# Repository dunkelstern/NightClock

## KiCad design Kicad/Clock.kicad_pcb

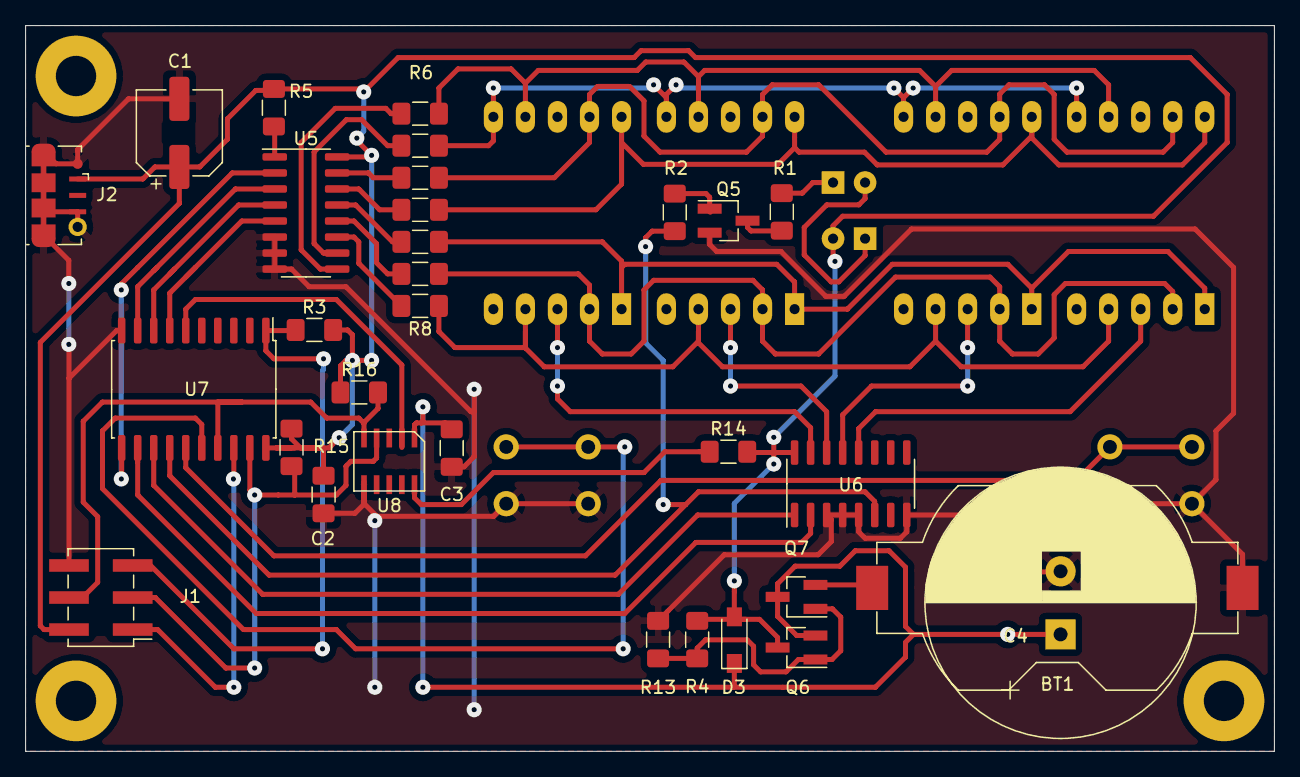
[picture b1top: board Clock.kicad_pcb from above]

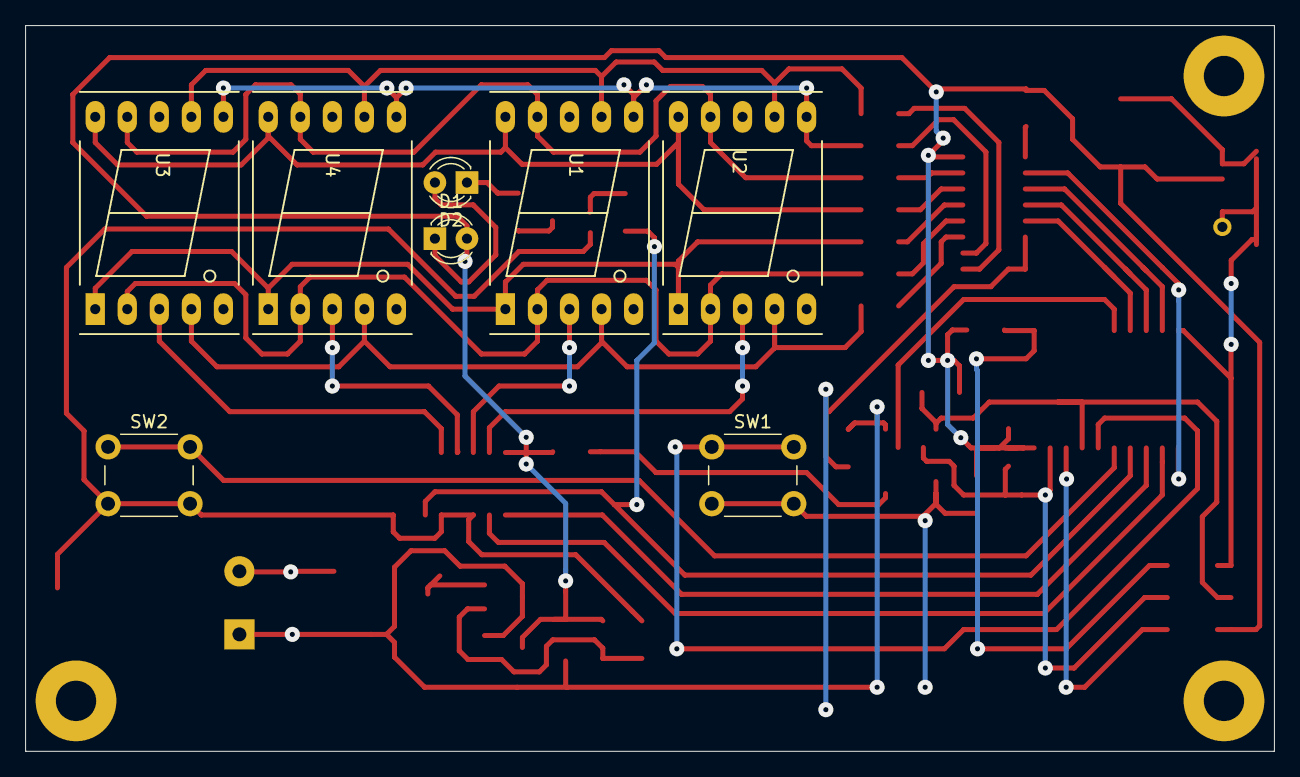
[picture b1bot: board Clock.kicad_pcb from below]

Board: 2 copper layers, 99.0 x 57.5 mm, 39 parts (8 on the bottom side), 43 nets.

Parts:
BT1: Battery_Cell; BatteryHolder_Keystone_1058_1x2032
C1: 4.7uF; CP_Elec_6.3x5.7
C2, C3: 100nF; C_1206_3216Metric_Pad1.42x1.75mm_HandSolder
C4: 1F; CP_Radial_D14.0mm_P5.00mm
D1, D2: LED; LED_D3.0mm
D3: D; D_SOD-123
J1: AVR-ISP-6; PinHeader_2x03_P2.54mm_Vertical_SMD
J2: USB_B_Micro; USB_Micro-B_Molex-105017-0001
Q5: BC848; SOT-23_Handsoldering
Q6: BC848C; SOT-23_Handsoldering
Q7: BC858A; SOT-23_Handsoldering
R1: 120; R_1206_3216Metric_Pad1.42x1.75mm_HandSolder
R2, R4: 1k; R_1206_3216Metric_Pad1.42x1.75mm_HandSolder
R3, R5, R14: 10k; R_1206_3216Metric_Pad1.42x1.75mm_HandSolder
R6, R7, R8, R9, R10, R11: 150; R_1206_3216Metric_Pad1.42x1.75mm_HandSolder
R12: 160; R_1206_3216Metric_Pad1.42x1.75mm_HandSolder
R13: 100k; R_1206_3216Metric_Pad1.42x1.75mm_HandSolder
R15, R16: 4.7k; R_1206_3216Metric_Pad1.42x1.75mm_HandSolder
SW1: Inc; SW_PUSH_6mm_H13mm
SW2: Prgm; SW_PUSH_6mm_H13mm
U1, U2, U3, U4: KCSC02-123; 7SegmentLED_LTS6760_LTS6780
U5: 4543; SOIC-16_3.9x9.9mm_P1.27mm
U6: 74LS138; SOIC-16_3.9x9.9mm_P1.27mm
U7: ATtiny2313-20SU; SOIC-20W_7.5x12.8mm_P1.27mm
U8: RV-8564-C2

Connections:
+5V: C1.1, C2.1, D1.2, D3.2, J1.2, J2.1, Q6.3, R3.2, R4.2, R5.1, R14.2, R15.1, R16.1, U5.16, U6.16, U7.20
/PWM: R2.2, U6.6, U7.14
/a: R6.1, U1.7, U2.7, U3.7, U4.7
/a0: U6.1, U7.13
/a1: U6.2, U7.12
/b: R7.1, U1.6, U2.6, U3.6, U4.6
/c: R8.1, U1.4, U2.4, U3.4, U4.4
/d: R9.1, U1.2, U2.2, U3.2, U4.2
/d0: U5.5, U7.7
/d1: U5.3, U7.9
/d2: U5.2, U7.11
/d3: U5.4, U7.8
/e: R10.1, U1.1, U2.1, U3.1, U4.1
/f: R11.1, U1.9, U2.9, U3.9, U4.9
/g: R12.1, U1.10, U2.10, U3.10, U4.10
/l0: U3.3, U6.12
/l1: U4.3, U6.13
/l2: U1.3, U6.14
/l3: U2.3, U6.15
BAT_BACKUP: C3.1, C4.1, D3.1, Q6.2, Q7.3, U8.1
GND: BT1.2, C1.2, C2.2, C3.2, C4.2, J1.6, J2.5, J2.6, Q5.2, R13.2, SW1.2, SW2.2, U5.6, U5.7, U5.8, U6.3, U6.4, U6.5, U6.8, U7.10, U8.6
INC_BTN: SW1.1, U7.16
unnamed: BT1.1, Q7.2
unnamed: D1.1, D2.2
unnamed: D2.1, R1.1
unnamed: J1.1, U7.18
unnamed: J1.3, R15.2, U7.19, U8.4
unnamed: J1.4, R16.2, U7.17, U8.5
unnamed: J1.5, R3.1, U7.1
unnamed: Q5.1, R2.1
unnamed: Q5.3, R1.2
unnamed: Q6.1, Q7.1, R4.1, R13.1
unnamed: R5.2, U5.1
unnamed: R6.2, U5.9
unnamed: R7.2, U5.10
unnamed: R8.2, U5.11
unnamed: R9.2, U5.12
unnamed: R10.2, U5.13
unnamed: R11.2, U5.15
unnamed: R12.2, U5.14
unnamed: R14.1, U8.10
unnamed: U7.6, U8.2
PRGM_BTN: SW2.1, U7.15

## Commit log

2019-09-04 KiCAD PCB
2019-09-04 Attiny2313 Source code
2019-09-04 Add PDF documentation for all chips
2019-09-04 Create LICENSE
2019-09-05 Update gitignore
2019-09-05 Add Makefile to be able to compile without Atmel Studio
2019-09-05 Some Updates
    - Run the ATTiny on 8MHz
    - Increase refresh rate
    - Increase brightness range
    - Darker minimal brightness
    - Minimal brightness dependant on time of day updated hourly
2019-09-05 Add hex file for Firmware
2019-09-05 Update Atmel Studio c project to 8MHz clock
2019-09-05 Add Gerbers to fabrication
2019-09-05 Update PCB silkscreen
2019-09-05 Flip Supercap to other board side
2019-09-05 PCB Step file
2019-09-05 Case Fusion360 Archive
2019-09-05 STL Fabrication Files
